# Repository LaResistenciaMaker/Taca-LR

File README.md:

# Proyecto taca-taca
## Requerimientos:

- [x] Armar estructura a medida para el taca
- [x] Instalar sistema de luces LED en la estructura
- [x] Diseñar un sistema basado en displays 7 segmentos
- [x] Diseño de placa PCB
- [ ] Programación para contador de goles
- [ ] Montar botones y cableado
- [ ] Definir sistema de alimentación e instalarlo

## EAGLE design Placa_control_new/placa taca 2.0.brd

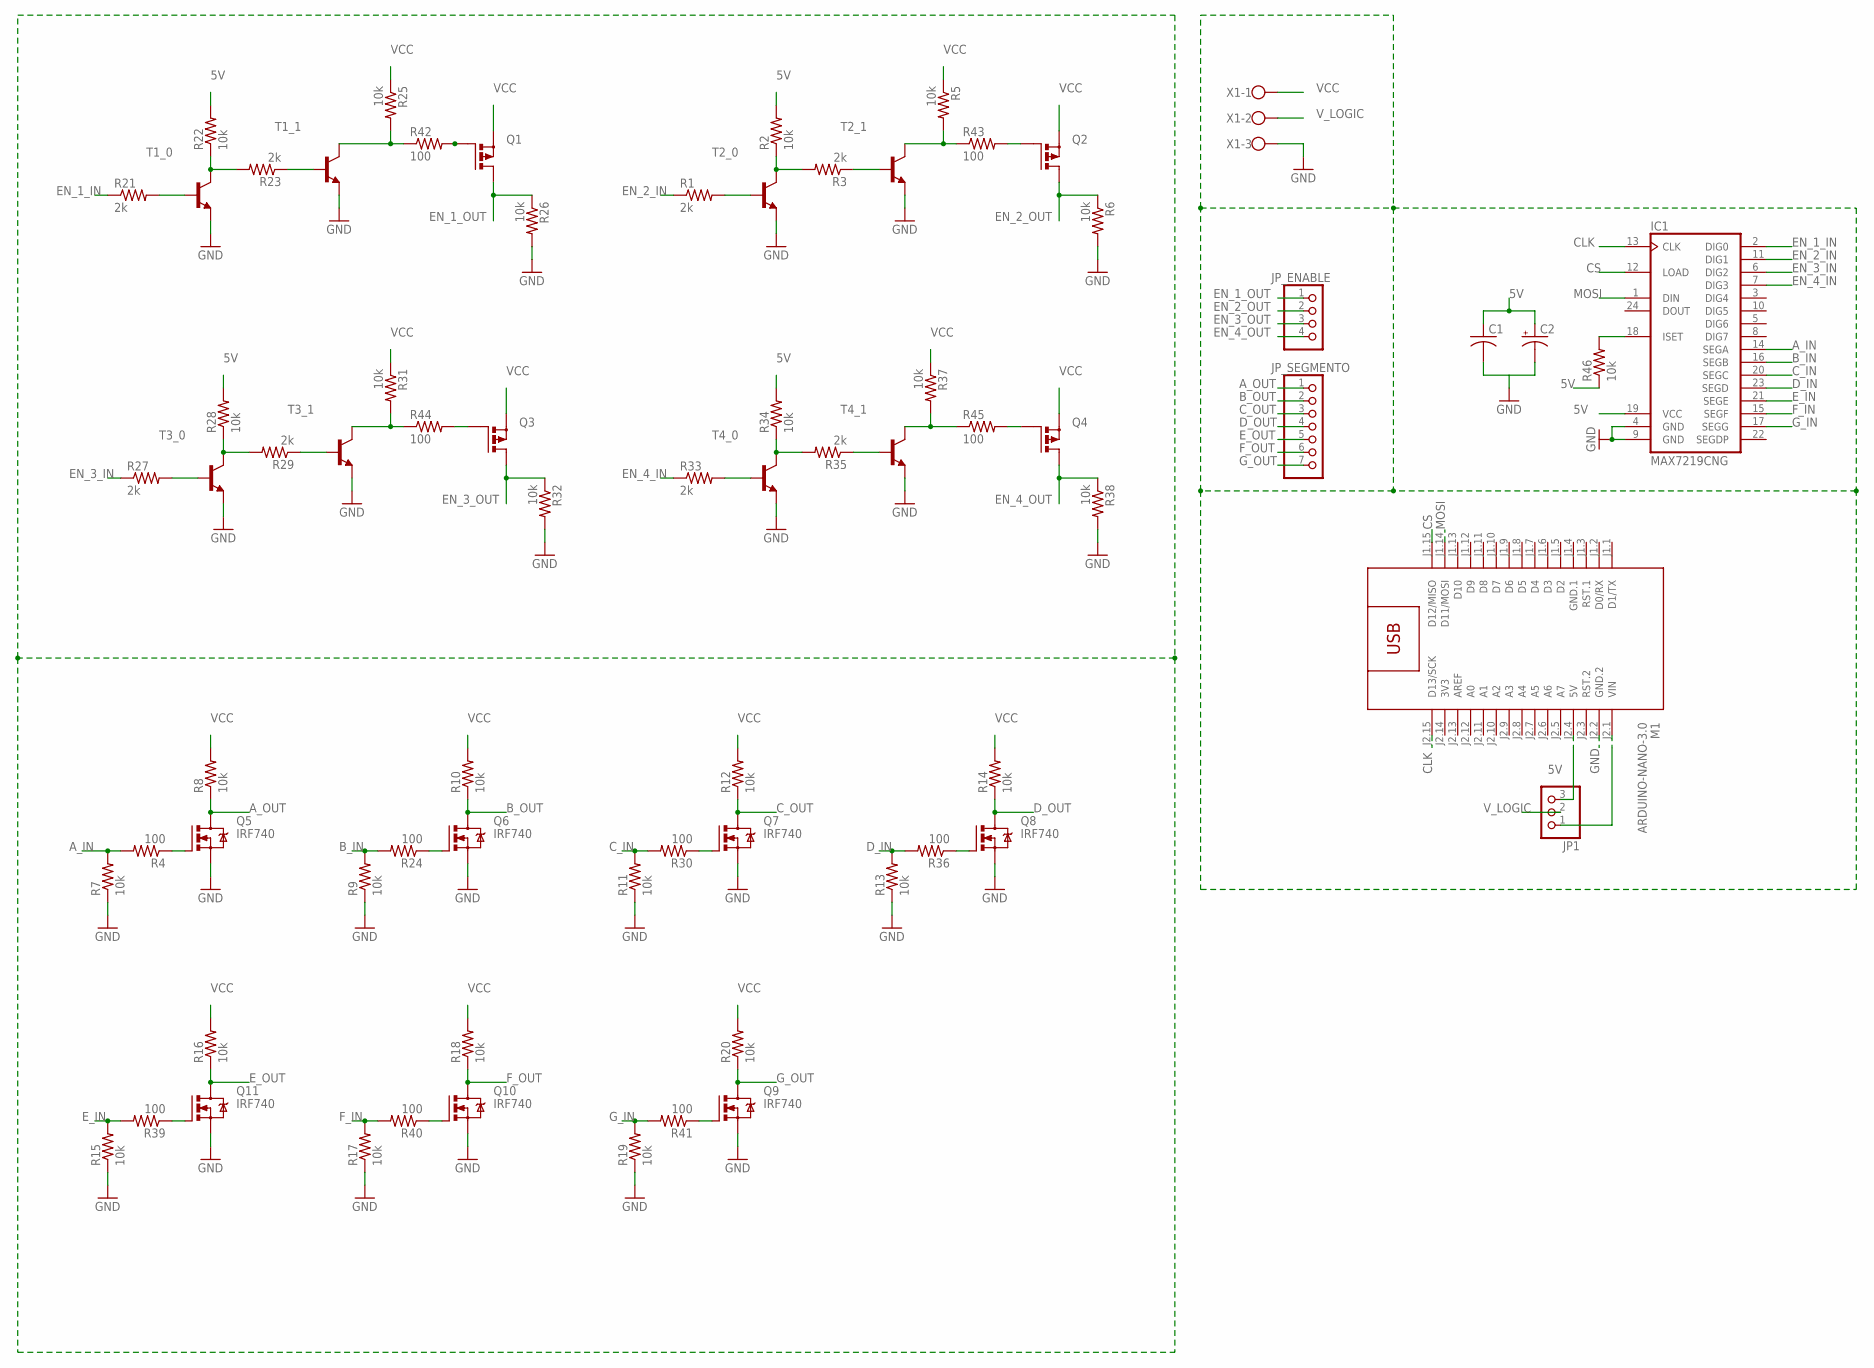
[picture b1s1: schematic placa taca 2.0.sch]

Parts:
C1: C-US025-030X050; C025-030X050
C2: CPOL-USE2.5-5; E2,5-5
IC1: MAX7219CNG; DIL24-3
JP1: PINHD-1X3; 1X03
JP_ENABLE: PINHD-1X4; 1X04
JP_SEGMENTO: PINHD-1X7; 1X07
M1: ARDUINO-NANO-3.0
Q1, Q2, Q3, Q4: PMOSFET_PTO220BV; TO220BV
Q5, Q6, Q7, Q8, Q9, Q10, Q11: IRF740; TO220BV
R1, R3, R21, R23, R27, R29, R33, R35: 2k; 0207/10
R2, R5, R6, R7, R8, R9, R10, R11, R12, R13, R14, R15, R16, R17, R18, R19, R20, R22, R25, R26, R28, R31, R32, R34, R37, R38, R46: 10k; 0207/10
R4, R24, R30, R36, R39, R40, R41, R42, R43, R44, R45: 100; 0207/10
T1_0, T1_1, T2_0, T2_1, T3_0, T3_1, T4_0, T4_1: 2N2222-NPN-TO92-EBC; TO92-EBC
X1: W237-103

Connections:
3V3: M1.J2.14 (3V3)
5V: C1.1, C2.+, IC1.19 (VCC), JP1.3, M1.J2.4 (5V), R2.2, R22.2, R28.2, R34.2, R46.1
A_IN: IC1.14 (SEGA), R4.2, R7.2
A_OUT: JP_SEGMENTO.1, Q5.D, R8.1
B_IN: IC1.16 (SEGB), R9.2, R24.2
B_OUT: JP_SEGMENTO.2, Q6.D, R10.1
CLK: IC1.13 (CLK), M1.J2.15 (D13/SCK)
CS: IC1.12 (LOAD), M1.J1.15 (D12/MISO)
C_IN: IC1.20 (SEGC), R11.2, R30.2
C_OUT: JP_SEGMENTO.3, Q7.D, R12.1
D_IN: IC1.23 (SEGD), R13.2, R36.2
D_OUT: JP_SEGMENTO.4, Q8.D, R14.1
EN_1_IN: IC1.2 (DIG0), R21.1
EN_1_OUT: JP_ENABLE.1, Q1.D, R26.1
EN_2_IN: IC1.11 (DIG1), R1.1
EN_2_OUT: JP_ENABLE.2, Q2.D, R6.1
EN_3_IN: IC1.6 (DIG2), R27.1
EN_3_OUT: JP_ENABLE.3, Q3.D, R32.1
EN_4_IN: IC1.7 (DIG3), R33.1
EN_4_OUT: JP_ENABLE.4, Q4.D, R38.1
E_IN: IC1.21 (SEGE), R15.2, R39.2
E_OUT: JP_SEGMENTO.5, Q11.D, R16.1
F_IN: IC1.15 (SEGF), R17.2, R40.2
F_OUT: JP_SEGMENTO.6, Q10.D, R18.1
G_IN: IC1.17 (SEGG), R19.2, R41.2
G_OUT: JP_SEGMENTO.7, Q9.D, R20.1
MOSI: IC1.1 (DIN), M1.J1.14 (D11/MOSI)
unnamed: R1.2, T2_0.B
unnamed: R2.1, R3.2, T2_0.C
unnamed: R3.1, T2_1.B
unnamed: R5.2, R43.1, T2_1.C
unnamed: Q5.G, R4.1
unnamed: Q6.G, R24.1
unnamed: Q7.G, R30.1
unnamed: Q8.G, R36.1
unnamed: Q1.G, R42.2
unnamed: Q10.G, R40.1
unnamed: Q9.G, R41.1
unnamed: Q2.G, R43.2
unnamed: Q3.G, R44.2
unnamed: Q4.G, R45.2
unnamed: IC1.18 (ISET), R46.2
unnamed: Q11.G, R39.1
unnamed: JP1.1, M1.J2.1 (VIN)
unnamed: R21.2, T1_0.B
unnamed: R22.1, R23.2, T1_0.C
unnamed: R23.1, T1_1.B
unnamed: R25.2, R42.1, T1_1.C
unnamed: R27.2, T3_0.B
unnamed: R28.1, R29.2, T3_0.C
unnamed: R29.1, T3_1.B
unnamed: R31.2, R44.1, T3_1.C
unnamed: R33.2, T4_0.B
unnamed: R34.1, R35.2, T4_0.C
unnamed: R35.1, T4_1.B
unnamed: R37.2, R45.1, T4_1.C
VCC: Q1.S, Q2.S, Q3.S, Q4.S, R5.1, R8.2, R10.2, R12.2, R14.2, R16.2, R18.2, R20.2, R25.1, R31.1, R37.1, X1.1
V_LOGIC: JP1.2, X1.2

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
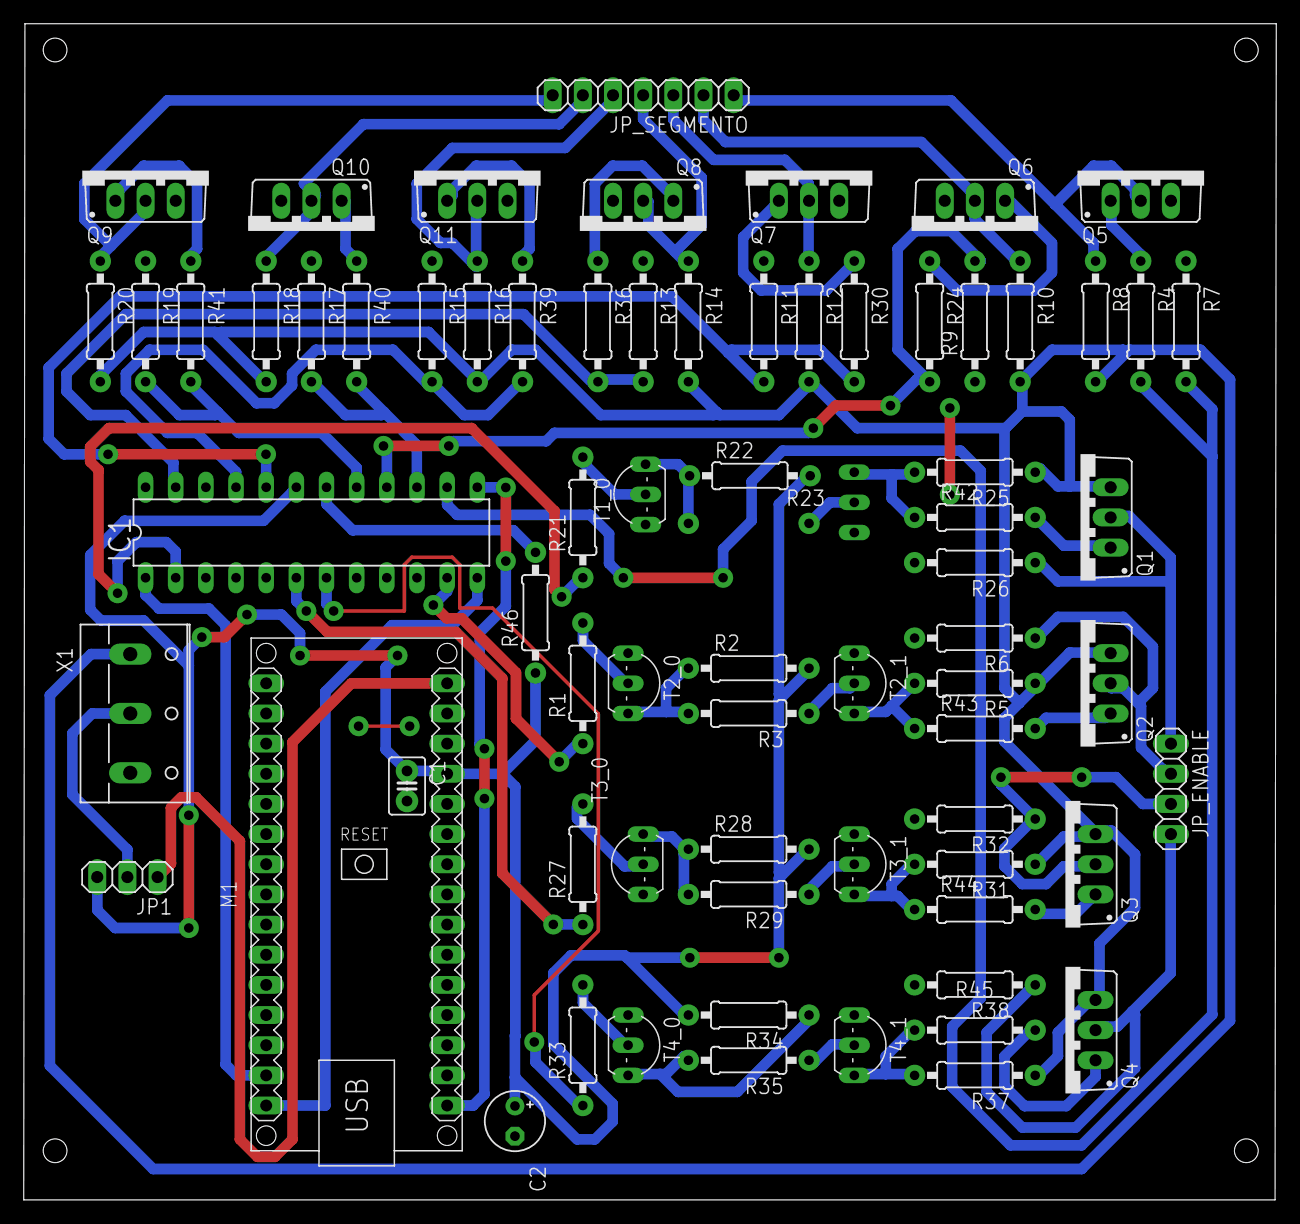
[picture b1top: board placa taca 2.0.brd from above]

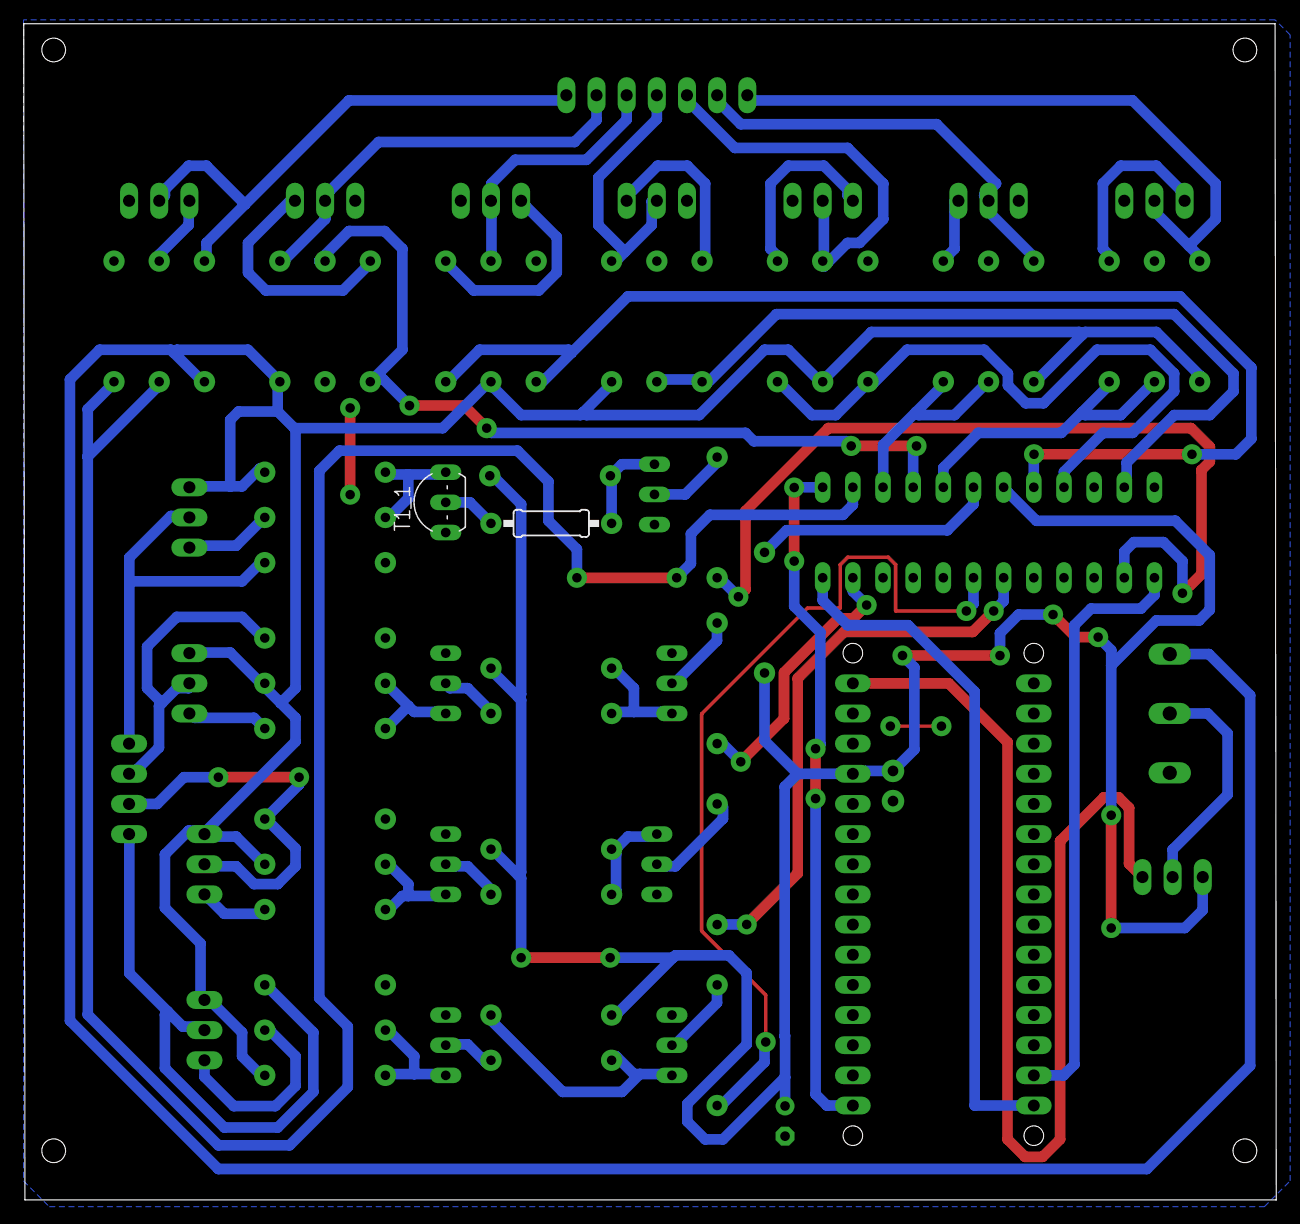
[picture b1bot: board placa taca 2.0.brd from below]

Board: 2 copper layers, 105.5 x 99.1 mm, 73 parts (2 on the bottom side), 58 nets.

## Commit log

2019-09-13 Actualizacion de la placa y codigo demo
2019-09-15 :pencil: Readme Actualizado
2019-10-03 :bento: Actualizacion placa v2.0
2019-10-03 :mute: Eliminar logs viejos

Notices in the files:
parts and their libraries:
diy-modules: Released under the Creative Commons Attribution 4.0 International License: http://creativecommons.org/licenses/by/4.0
